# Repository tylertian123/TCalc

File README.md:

# TCalc
Source code for an STM32 calculator. This repository contains the firmware source code for both the main and keyboard processors as well as the custom schematics.

Some notable features:
* Full math expression display engine
* Multi-function graphing
* Support for custom variable and function definitions
* Basic linear algebra capabilities
* Useful built-in functions such as linear system solver, polynomial regression, etc
* Built-in periodic table with extensive information for every element
* Snake and Tetris mini-games
* [Here's it playing Bad Apple because why not.](https://youtu.be/kNUgEzcHYEs) [[Separate repo here]](https://github.com/tylertian123/tcalc-badapple)

## Gallery

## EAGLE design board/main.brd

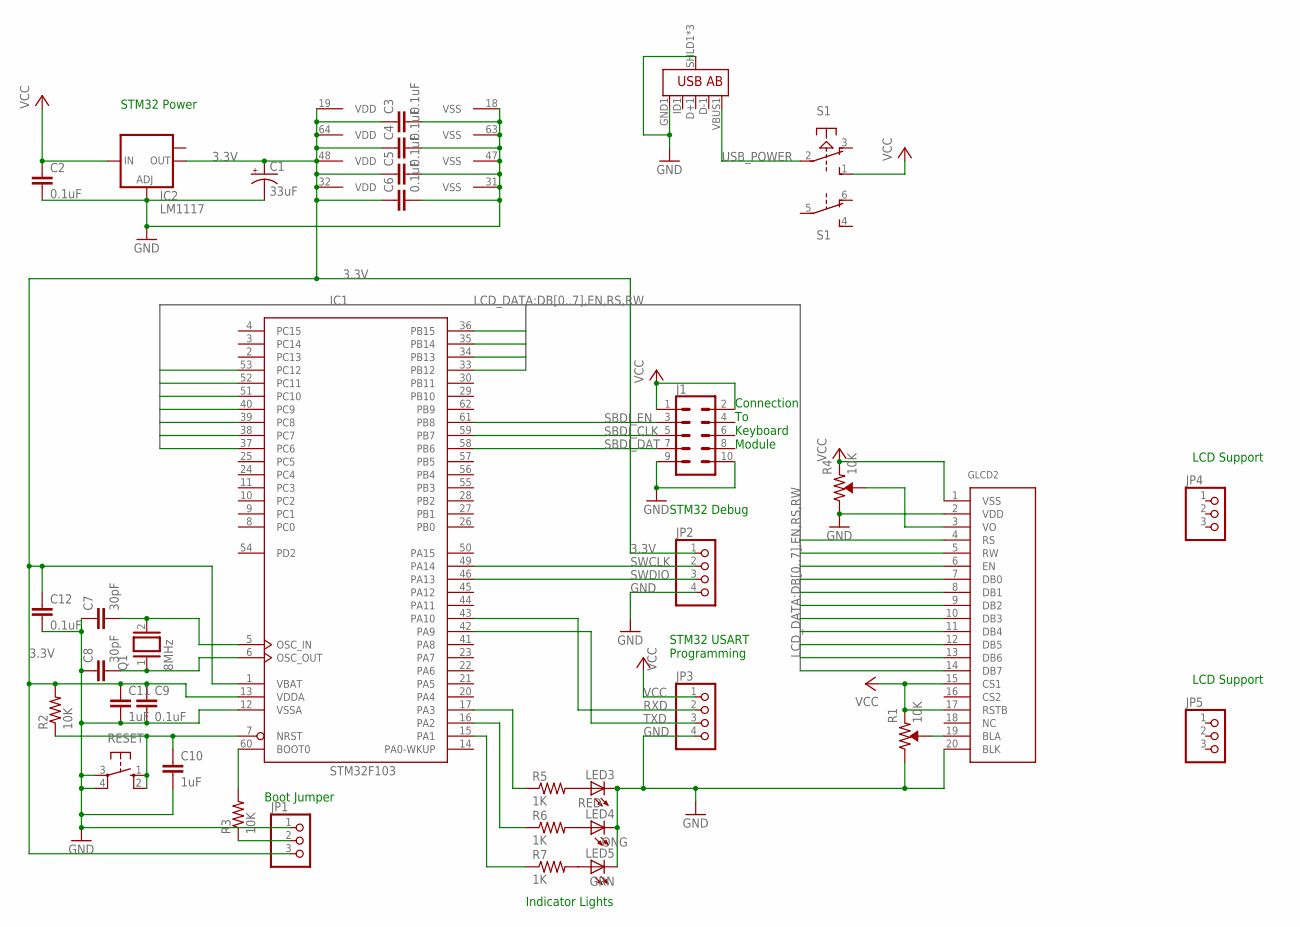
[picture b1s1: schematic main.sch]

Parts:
C1: 33uF; E2-5
C2, C3, C4, C5, C6, C9, C12: 0.1uF; C025-025X050
C7, C8: 30pF; C025-025X050
C10, C11: 1uF; C025-025X050
GLCD2: LCD128X64; GLCD_TRULY_128X64_20_PINES
IC1: STM32F103; LQFP64
IC2: LM1117; SOT223
J1: CONN_05X2SHD_LOCK; 2X5-SHROUDED_LOCK
JP1, JP4, JP5: PINHD-1X3; 1X03
JP2, JP3: PINHD-1X4; 1X04
LED3: RED; LED5MM
LED4: ONG; LED5MM
LED5: GRN; LED5MM
Q1: 8MHz; QS
R1, R4: 10K; TRIMPOT-PTH-3386U
R2, R3: 10K; 0204/7
R5, R6, R7: 1K; 0204/7
RESET: 10-XX; B3F-10XX
S1: PVA2R
U1: USB_AB_SMT; USB-AB-MICRO-SMD

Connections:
3.3V: C1.+, C3.1, C4.1, C5.1, C6.1, C9.1, C11.1, C12.1, IC1.1 (VBAT), IC1.13 (VDDA), IC1.19 (VDD), IC1.32 (VDD), IC1.48 (VDD), IC1.64 (VDD), IC2.2 (OUT), JP1.3, JP2.1, R2.2
DB0: GLCD2.7 (DB0), IC1.33 (PB12)
DB1: GLCD2.8 (DB1), IC1.34 (PB13)
DB2: GLCD2.9 (DB2), IC1.35 (PB14)
DB3: GLCD2.10 (DB3), IC1.36 (PB15)
DB4: GLCD2.11 (DB4), IC1.37 (PC6)
DB5: GLCD2.12 (DB5), IC1.38 (PC7)
DB6: GLCD2.13 (DB6), IC1.39 (PC8)
DB7: GLCD2.14 (DB7), IC1.40 (PC9)
EN: GLCD2.6 (EN), IC1.53 (PC12)
GND: C1.-, C2.2, C3.2, C4.2, C5.2, C6.2, C7.1, C8.1, C9.2, C10.2, C11.2, C12.2, GLCD2.2 (VDD), GLCD2.20 (BLK), IC1.12 (VSSA), IC1.18 (VSS), IC1.31 (VSS), IC1.47 (VSS), IC1.63 (VSS), IC2.1 (ADJ), J1.9, J1.10, JP1.1, JP2.4, JP3.4, LED3.K (C), LED4.K (C), LED5.K (C), R1.1, R4.1, RESET.3, RESET.4 (P1), U1.GND1 (GND), U1.SHLD1 (SHIELD), U1.SHLD2 (SHIELD), U1.SHLD3 (SHIELD)
unnamed: GLCD2.19 (BLA), R1.2
unnamed: GLCD2.3 (VO), R4.2
unnamed: LED3.A, R5.2
unnamed: LED4.A, R6.2
unnamed: C7.2, IC1.5 (OSC_IN), Q1.2
unnamed: C10.1, IC1.7 (NRST), R2.1, RESET.1 (S), RESET.2 (S1)
unnamed: C8.2, IC1.6 (OSC_OUT), Q1.1
unnamed: IC1.15 (PA1), R7.1
unnamed: IC1.60 (BOOT0), R3.2
unnamed: JP1.2, R3.1
unnamed: IC1.16 (PA2), R6.1
unnamed: IC1.17 (PA3), R5.1
unnamed: LED5.A, R7.2
RS: GLCD2.4 (RS), IC1.51 (PC10)
RW: GLCD2.5 (RW), IC1.52 (PC11)
RXD: IC1.43 (PA10), JP3.2
SBDI_CLK: IC1.59 (PB7), J1.5
SBDI_DAT: IC1.58 (PB6), J1.7
SBDI_EN: IC1.61 (PB8), J1.3
SWCLK: IC1.49 (PA14), JP2.2
SWDIO: IC1.46 (PA13), JP2.3
TXD: IC1.42 (PA9), JP3.3
USB_POWER: S1.2, U1.VBUS1 (VBUS)
VCC: C2.1, GLCD2.1 (VSS), GLCD2.15 (CS1), GLCD2.17 (RSTB), IC2.3 (IN), J1.1, J1.2, JP3.1, R1.3, R4.3, S1.1 (S)

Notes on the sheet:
STM32 Power
Boot Jumper
STM32 Debug
STM32 USART Programming
Indicator Lights
LCD Support
Connection To Keyboard Module

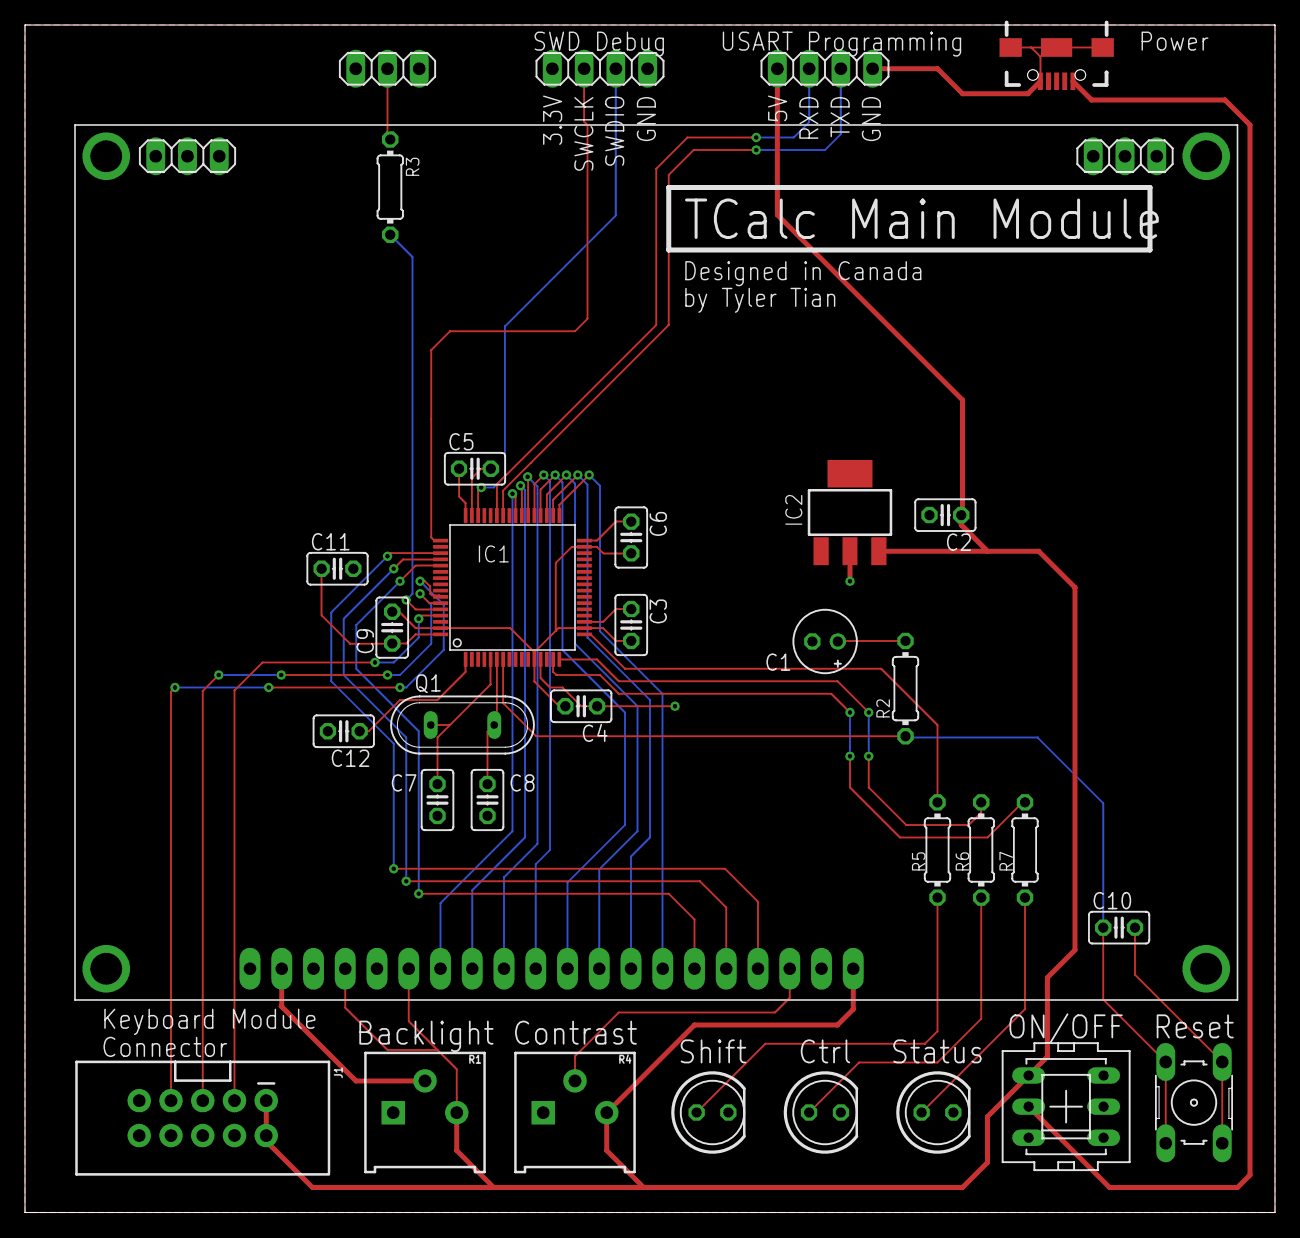
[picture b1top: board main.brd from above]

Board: 2 copper layers, 100.0 x 95.0 mm, 35 parts (0 on the bottom side), 35 nets.

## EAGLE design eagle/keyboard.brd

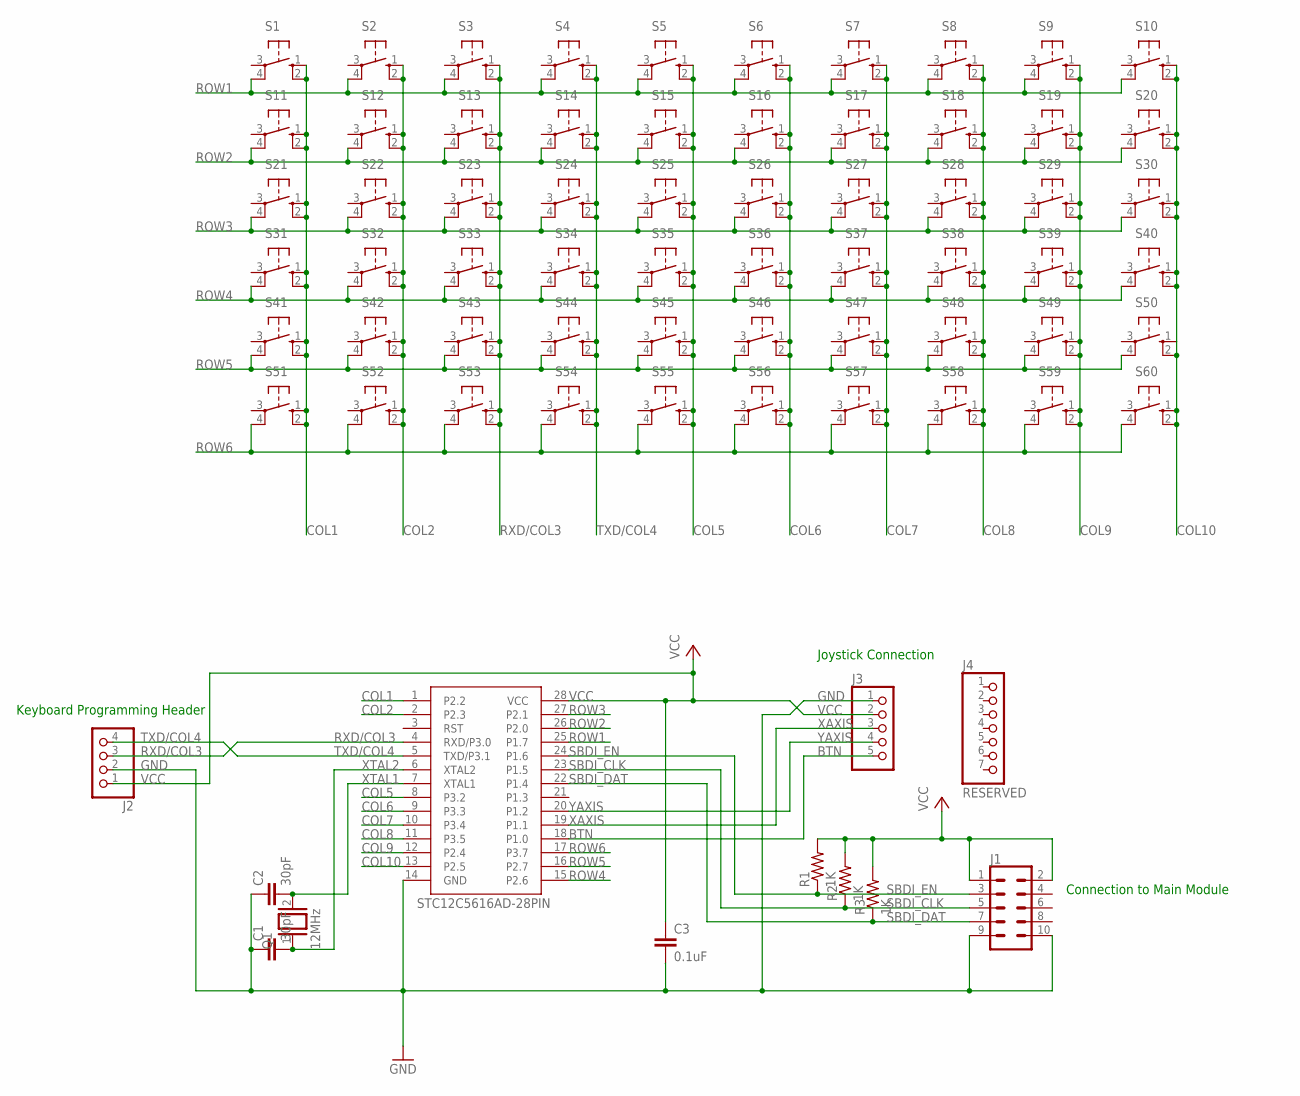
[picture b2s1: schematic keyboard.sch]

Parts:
C1, C2: 30pF; C025-025X050
C3: 0.1uF; C025-030X050
IC1: STC12C5616AD; DIP787W45P254L3505H508Q28B
J1: CONN_05X2SHD_LOCK; 2X5-SHROUDED_LOCK
J2: PINHD-1X4; 1X04
J3: PINHD-1X5; 1X05
J4: RESERVED; 1X07
Q1: 12MHz; QS
R1, R2, R3: 1K; 0204/7
S1, S2, S3, S4, S5, S6, S7, S8, S9, S10, S11, S12, S13, S14, S15, S16, S17, S18, S19, S20, S21, S22, S23, S24, S25, S26, S27, S28, S29, S30, S31, S32, S33, S34, S35, S36, S37, S38, S39, S40, S41, S42, S43, S44, S45, S46, S47, S48, S49, S50, S51, S52, S53, S54, S55, S56, S57, S58, S59, S60: 10-XX; B3F-10XX

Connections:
BTN: IC1.18 (P1.0), J3.5
COL1: IC1.1 (P2.2), S1.1 (S), S1.2 (S1), S11.1 (S), S11.2 (S1), S21.1 (S), S21.2 (S1), S31.1 (S), S31.2 (S1), S41.1 (S), S41.2 (S1), S51.1 (S), S51.2 (S1)
COL2: IC1.2 (P2.3), S2.1 (S), S2.2 (S1), S12.1 (S), S12.2 (S1), S22.1 (S), S22.2 (S1), S32.1 (S), S32.2 (S1), S42.1 (S), S42.2 (S1), S52.1 (S), S52.2 (S1)
COL5: IC1.8 (P3.2), S5.1 (S), S5.2 (S1), S15.1 (S), S15.2 (S1), S25.1 (S), S25.2 (S1), S35.1 (S), S35.2 (S1), S45.1 (S), S45.2 (S1), S55.1 (S), S55.2 (S1)
COL6: IC1.9 (P3.3), S6.1 (S), S6.2 (S1), S16.1 (S), S16.2 (S1), S26.1 (S), S26.2 (S1), S36.1 (S), S36.2 (S1), S46.1 (S), S46.2 (S1), S56.1 (S), S56.2 (S1)
COL7: IC1.10 (P3.4), S7.1 (S), S7.2 (S1), S17.1 (S), S17.2 (S1), S27.1 (S), S27.2 (S1), S37.1 (S), S37.2 (S1), S47.1 (S), S47.2 (S1), S57.1 (S), S57.2 (S1)
COL8: IC1.11 (P3.5), S8.1 (S), S8.2 (S1), S18.1 (S), S18.2 (S1), S28.1 (S), S28.2 (S1), S38.1 (S), S38.2 (S1), S48.1 (S), S48.2 (S1), S58.1 (S), S58.2 (S1)
COL9: IC1.12 (P2.4), S9.1 (S), S9.2 (S1), S19.1 (S), S19.2 (S1), S29.1 (S), S29.2 (S1), S39.1 (S), S39.2 (S1), S49.1 (S), S49.2 (S1), S59.1 (S), S59.2 (S1)
COL10: IC1.13 (P2.5), S10.1 (S), S10.2 (S1), S20.1 (S), S20.2 (S1), S30.1 (S), S30.2 (S1), S40.1 (S), S40.2 (S1), S50.1 (S), S50.2 (S1), S60.1 (S), S60.2 (S1)
GND: C1.1, C2.1, C3.2, IC1.14 (GND), J1.9, J1.10, J2.2, J3.1; also elsewhere on the board
unnamed 10: IC1.3 (RST); also elsewhere on the board
ROW1: IC1.25 (P1.7), S1.4 (P1), S2.4 (P1), S3.4 (P1), S4.4 (P1), S5.4 (P1), S6.4 (P1), S7.4 (P1), S8.4 (P1), S9.4 (P1), S10.4 (P1)
ROW2: IC1.26 (P2.0), S11.4 (P1), S12.4 (P1), S13.4 (P1), S14.4 (P1), S15.4 (P1), S16.4 (P1), S17.4 (P1), S18.4 (P1), S19.4 (P1), S20.4 (P1)
ROW3: IC1.27 (P2.1), S21.4 (P1), S22.4 (P1), S23.4 (P1), S24.4 (P1), S25.4 (P1), S26.4 (P1), S27.4 (P1), S28.4 (P1), S29.4 (P1), S30.4 (P1)
ROW4: IC1.15 (P2.6), S31.4 (P1), S32.4 (P1), S33.4 (P1), S34.4 (P1), S35.4 (P1), S36.4 (P1), S37.4 (P1), S38.4 (P1), S39.4 (P1), S40.4 (P1)
ROW5: IC1.16 (P2.7), S41.4 (P1), S42.4 (P1), S43.4 (P1), S44.4 (P1), S45.4 (P1), S46.4 (P1), S47.4 (P1), S48.4 (P1), S49.4 (P1), S50.4 (P1)
ROW6: IC1.17 (P3.7), S51.4 (P1), S52.4 (P1), S53.4 (P1), S54.4 (P1), S55.4 (P1), S56.4 (P1), S57.4 (P1), S58.4 (P1), S59.4 (P1), S60.4 (P1)
RXD/COL3: IC1.4 (RXD/P3.0), J2.3, S3.1 (S), S3.2 (S1), S13.1 (S), S13.2 (S1), S23.1 (S), S23.2 (S1), S33.1 (S), S33.2 (S1), S43.1 (S), S43.2 (S1), S53.1 (S), S53.2 (S1)
SBDI_CLK: IC1.23 (P1.5), J1.5, R2.1
SBDI_DAT: IC1.22 (P1.4), J1.7, R3.1
SBDI_EN: IC1.24 (P1.6), J1.3, R1.1
TXD/COL4: IC1.5 (TXD/P3.1), J2.4, S4.1 (S), S4.2 (S1), S14.1 (S), S14.2 (S1), S24.1 (S), S24.2 (S1), S34.1 (S), S34.2 (S1), S44.1 (S), S44.2 (S1), S54.1 (S), S54.2 (S1)
VCC: C3.1, IC1.28 (VCC), J1.1, J1.2, J2.1, J3.2, R1.2, R2.2, R3.2; also elsewhere on the board
XAXIS: IC1.19 (P1.1), J3.3
XTAL1: C2.2, IC1.7 (XTAL1), Q1.2
XTAL2: C1.2, IC1.6 (XTAL2), Q1.1
YAXIS: IC1.20 (P1.2), J3.4

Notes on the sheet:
Keyboard Programming Header
Joystick Connection
Connection to Main Module

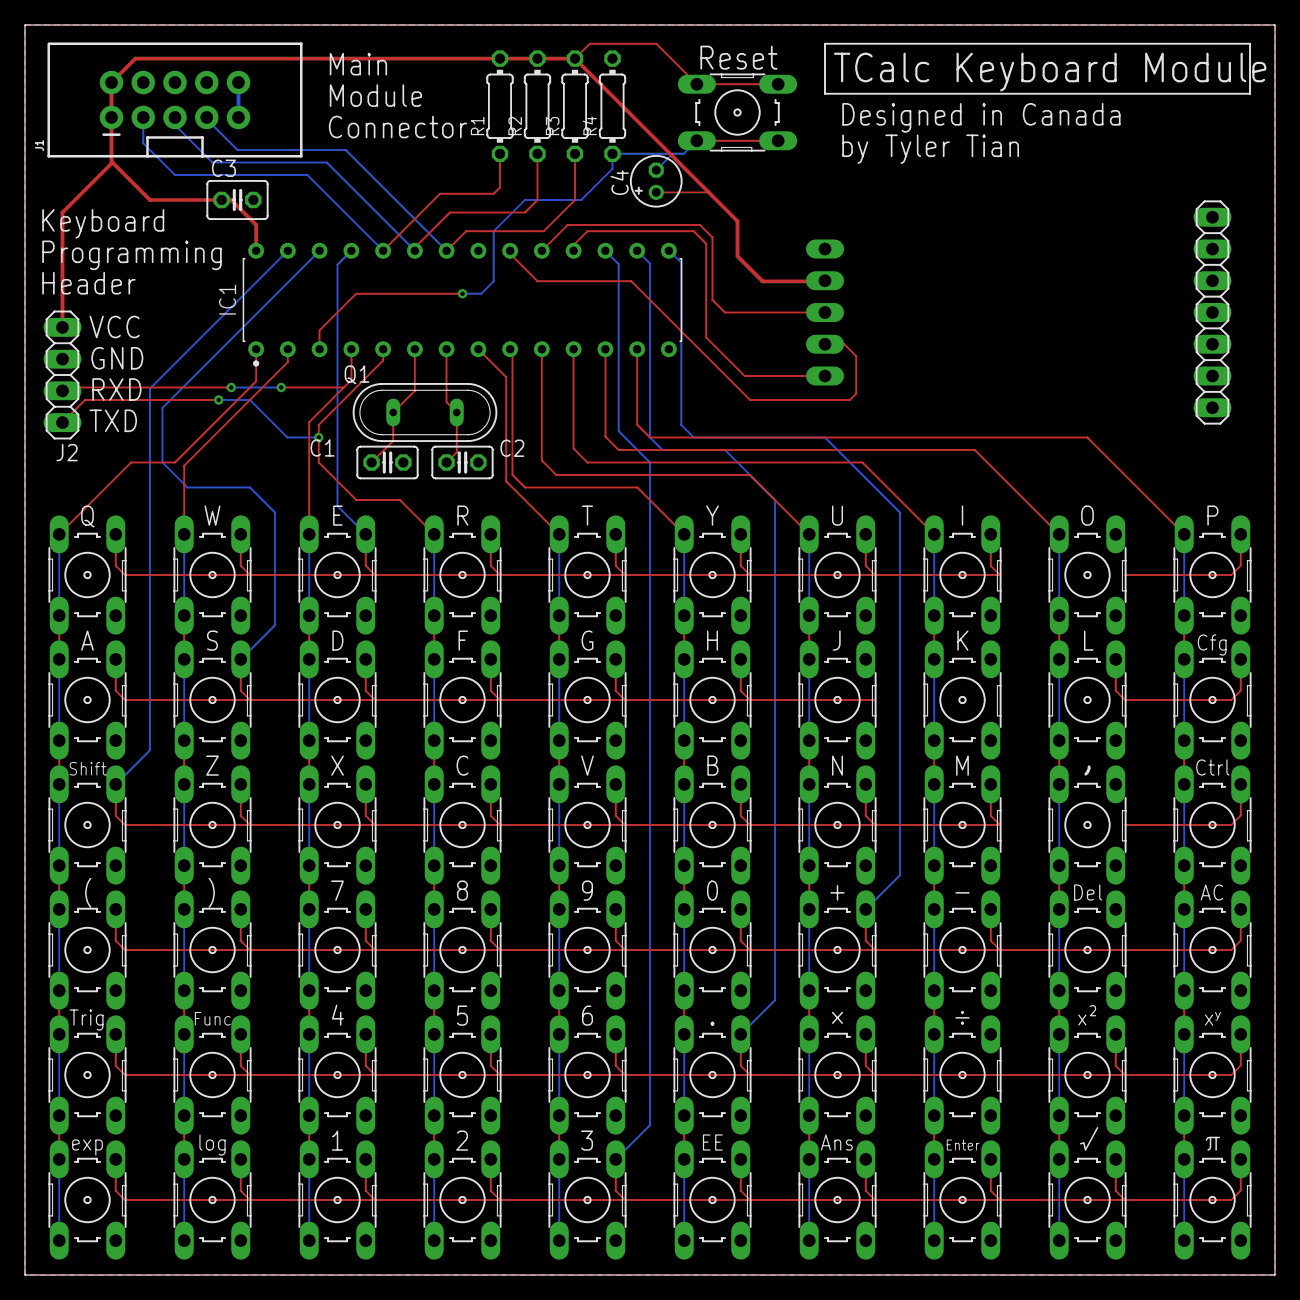
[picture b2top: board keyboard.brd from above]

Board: 2 copper layers, 100.0 x 100.0 mm, 75 parts (1 on the bottom side), 27 nets.

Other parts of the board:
C4: 10uF; E1,8-4
R4: 10K; 0204/7
S61: B3F-10XX

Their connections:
GND: R4.2; also elsewhere on the board
unnamed 10: C4.-, R4.1, S61.3, S61.4; also elsewhere on the board
VCC: C4.+, S61.1, S61.2; also elsewhere on the board

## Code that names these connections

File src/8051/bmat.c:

#include "bmat.h"

void bmat_delay (unsigned int a){
	unsigned int i;
	while( --a != 0){
		for(i = 0; i < 600; i++);
	}
}

void resetRows() {
	ROW1 = ROW2 = ROW3 = ROW4 = ROW5 = ROW6 = 1;
}
void resetCols() {
	COL1 = COL2 = COL3 = COL4 = COL5 = COL6 = COL7 = COL8 = COL9 = COL10 = 1;
}

unsigned char checkCols() {
	if(!COL1) {
		//DEBOUNCE(COL1);
		return 0;
	}
	if(!COL2) {
		//DEBOUNCE(COL2);
		return 1;
	}
	if(!COL3) {
		//DEBOUNCE(COL3);
		return 2;
	}
	if(!COL4) {
		//DEBOUNCE(COL4);
		return 3;
	}
	if(!COL5) {
		//DEBOUNCE(COL5);
		return 4;
	}
	if(!COL6) {
		//DEBOUNCE(COL6);
		return 5;
	}
	if(!COL7) {
		//DEBOUNCE(COL7);
		return 6;
	}
	if(!COL8) {
		//DEBOUNCE(COL8);
		return 7;
	}
	if(!COL9) {
		//DEBOUNCE(COL9);
		return 8;
	}
	if(!COL10) {
		//DEBOUNCE(COL10);
		return 9;
	}
	return 0xFF;
}

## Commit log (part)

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2018-12-14 Add simple incomplete support for multiple arguments
2018-12-14 Fix memory leaks
2018-12-14 Fix bug in ntoa
2018-12-15 Add code for evaluating user-defined functions
2018-12-16 Add basic implementation of defining functions
2018-12-17 Add new round function
2018-12-18 Change signature of Function::compute
2018-12-18 Add function catalogue
2018-12-18 Overload call operator of eval::Operator
2018-12-19 Remap some keys and add function definition recall
2018-12-24 Check in eagle schs
2018-12-24 Fix schematic button matrix
2018-12-24 Add silkscreen
2018-12-25 Restore accidentally deleted file
2018-12-25 Finish basic component placement
2018-12-25 Add silkscreen labels
2018-12-26 Reexport gerbers
2018-12-26 Improve silkscreen
2018-12-27 Reroute main board
2019-06-25 Change port defs and fix interrupts
    Change port definitions for 8051 for the PCB design. Fix broken
    interrupts by adding calls to GPIO_EXTILineConfig.
2019-06-26 Add base for neda::Matrix
2019-06-26 Add matrix key in 8051 chip
2019-06-26 Fix neda::Matrix crashing bug
    Fix neda::Matrix crashing bug caused by the previous changing all
    indexes to be 0-based.
2019-06-27 Add matrix parsing in eval
2019-06-28 Add support for matrix addition, subtraction and multiplication
2019-06-28 Add support for matrix-scalar multiplication and division
2019-07-03 Add vector cross product for R3
2019-07-04 Add eval::Matrix::eliminate()
    Add new function to eval::Matrix that performs Gaussian elimination.
2019-07-04 Add identity matrix function
    Add built-in function I() which evaluates to an identity matrix of a
    specified dimension.
2019-07-04 Add result scrolling
    Add ability to scroll results that are too wide or too tall to fit on
    the screen.
2019-07-04 Reduce SBDI transmission speed
    Reduce SBDI transmission speed by 1/2 to prevent bad key readings.
2019-07-05 Change ifs to switches in eval code
    Change if...else if...else chains in eval::Operator::operator() into
    switch statements.
2019-07-05 Improve matrix drawing
    Centre expressions horizontally when drawing matrices.
2019-07-06 Remove unused characters and change division sign
    Comment out unused characters in font.cpp and change the division symbol
    to be the same as the slash.
2019-07-06 Add option to set number of significant digits
2019-07-08 Copy normal key press handling into exprentry.cpp
    Copy key press handling in normal (expression edit) mode into
    expr::ExprEntry.
2019-07-08 Copy remaining key handlers to exprentry
    Copy key handlers for config and matrix menus into expr::ExprEntry.
2019-07-08 Add new characters and update old characters
    Add new greater than or equal to and less than or equal to characters
    and update the old greater than and less than characters.
2019-07-09 Add eval code for piecewise functions
    Add code to evaluate piecewise functions.
2019-07-09 Add "else" clause in piecewise functions
    Add ability to specify an "else" clause in piecewise functions.
2019-07-09 Fix bug with expr::ExprEntry::adjustExpr()
    Fix bug where adjustExpr() sometimes positions the expression in the
    wrong location due to incorrect cursor info due to the locations of
    expressions not being updated.
2019-07-10 Change key enums
    Change key enums from sequential to randomized in the range from
    0x0000-0xFFFF inclusive. This means that now two bit flips (which would
    not be detected by the parity checking) is now less likely to generate
    another valid key combo.
2019-07-10 Fix shift light not turning off issue
    Fix shift light not turning off issue caused by an issue in the SBDI
    bus.
2019-07-11 Change key mappings on keyboard
    Move graph function selection to Ctrl+F and make Ctrl+G graph.
2019-07-11 Fix DrawBuf bugs and use in LCD12864
    Delegate drawing functions in LCD12864 to DrawBuf. Fix bugs in
    DrawBuf::setPixel and drawBuf::drawImage.
2019-07-11 Fix bugs in basic graphing code
2019-07-11 Fix bug and improve UI for graphing
    Fix bug where the screen will flicker when transitioning from graph
    viewer back to normal mode. Allow going into graph settings and graph
    function selection menues from the graph viewer.
2019-07-11 Add a cursor to the graph viewer
    Add a cursor in graph viewer mode that shows the X and Y coordinates.
2019-07-12 Create struct eval::Variable
    Create struct eval::Variable to replace the two separate arrays for
    variable names and variable values.
2019-07-16 Add new characters to LCD charset
    Add new logic operators to LCD charset, including AND, OR, XOR and NOT.
2019-07-17 Fix bug where logical operators treat undefined as true
    Fix bug where the logical operators AND, OR and XOR treat undefined
    values as if they were true.
2019-07-17 Fix bug introduced by commit 0b8f178
    Fix a bug introduced by commit 0b8f178 where the plus and minus
    operators will always be evaluated as unary operators regardless.
2019-07-17 Create unitconv.cpp and unitconv.hpp
    Create unitconv.cpp and unitconv.hpp, which convert between different
    units.
2019-07-21 Fix bug in neda::Matrix::copy() and neda::Piecewise::copy()
    Fix bug in Matrix and Piecewise's copy functions that causes the
    positioning of the copied expression to be messed up because they don't
    set the new expression's top spacing.
2019-07-21 Add key for subscript
    Bind Shift+Exponent to insert a subscript.
2019-07-21 Add null check when calling operators in eval::evaluate()
    When evaluating the expression by calling operators, add null checks in
    case the operation fails.
2019-07-21 Remove redundant built-in functions
    Remove redundant built-in functions transpose, inv, and I as they can
    now be done using a better syntax. Increase version to 1.2.7.
2019-07-21 Remove comparison operator keybinds
    Remove keybinds for the comparison operators greater than, less than,
    greater than or equal to, and less than or equal to since they can now
    be accessed through the logic menu.
2019-07-22 Add mini USART console
    Add a mini USART debug console, enabled by compiling with the
    _USE_CONSOLE macro.
2019-07-22 Add DynamicArray::createConstRef()
    Add a new DynamicArray static method createConstRef() that creates a
    const DynamicArray which just points to the memory specified by two
    iterators, thus avoiding having to allocate more memory and copying over
    elements. Use this new method in evaluate calls().
    Increase the result store count to 5.
2019-07-23 Add area units to conversion table
    Add area units to conversion table, including all units in the length
    units section squared, and hectares and acres. Modify findTokenEnd to
    allow names containing digits to allow this.
2019-07-24 Add stack overflow check to eval::evaluate
    Add a stack pointer check to eval::evaluate() to make sure that
    recursive functions without an exit condition does not cause a crash
    from stack overflow.
    Add command "stackinfo" to the console, which prints out the stack
    beginning and end addresses, stack size and current stack pointer.
    Increase version to 1.2.11.
2019-07-26 Allow matrix to be constructed from column vectors
    Allow the syntax where a matrix can be constructed from a row of column
    vectors.
2019-07-26 Add confirmation dialogs to clear var and all clear keys
    Pressing the clear var and all clear keys will now make a confirmation
    dialog appear to prevent being triggered accidentally.
2019-07-27 Change default increase amount in storage classes
    Change the default increase amount in Deque and DynamicArray from 1 to 8
    to make parsing expressions more efficient.
    Remove templates on eval::freeTokens and move its definition into
    eval.cpp.
2019-07-28 Delete unused files
    Delete unused files (starup_stm32f10x_md.s, stm32f10x_it.h and
    stm32f10x_it.c).
2019-07-29 Implement some operators for Numerical
    Implement operators += and -= for Numerical.
2019-07-29 Add more operators to util::Numerical
    Add == and != operators to util::Numerical.
2019-07-30 Add more operators and methods to util::Numerical
    Add operators < and > to util::Numerical and implement the pow() method
    for it.
2019-07-30 Change implementation of ltoa and ftoa
    Change implementation of ltoa and ftoa to use sprintf instead of doing
    the conversion themselves.
2019-07-31 Implement the fraction-format key
    Implement the fraction-format key to convert result display method from
    improper fractions to mixed numbers.
2019-09-01 Add useful graph viewer mode commands
    Add some useful graph viewer mode commands, including pressing h to
    "home" the cursor, pressing c to move the display window so that the
    cursor is centered, and pressing +/- to zoom in/out around the cursor.
2019-09-01 Add fast cursor movement in graph viewer
    Add feature where the cursor can be moved by 10 pixels each time in the
    graph viewer using the WASD keys.
2019-09-02 Change key enumeration and mapping code
    Change the key enumeration from random to sequential, which allows for a
    better algorithm that maps key code to characters which relies on the
    sequential order of keys for letters and numbers instead of using a
    switch statement.
2019-09-08 Create periodic table data
    Create files for periodic table stuff and add in some basic data for
    every element.
2019-09-18 Add code for periodic table outline
    Add code for displaying the outline of the periodic table.
2019-09-20 Add mean function
    Add a varargs mean function.
2019-09-23 Add basic element display
    Add basic element info display in periodic table mode.
2019-09-25 move to pio
2019-09-25 fix name
2019-09-26 fix ln from win
2019-09-27 Fix compile warnings
    Fix compile warnings due to using NULL in memset, adding brackets around
    && and missing default labels in switch statements.
2019-09-30 Add periodic table search functions
    Add periodic table functions to search by atomic number, symbol or name.
2019-10-02 Refactor drawString()
    Change the signature of lcd::DrawBuf::drawString() to now accept a set
    of flags telling it what to do (e.g. invert and alignment).
2019-10-06 Improve periodic table data
    Add electron configuration to periodic table data and fix bug of the
    valences of known noble gases being unknown.
2019-10-08 Add some processing for Tetris game
    Add some basic game logic for another hidden game - Tetris.
2019-10-08 Add DrawBuf::drawString vertical align flags
    Add the ability to specifiy vertical align in DrawBuf::drawString. Fix
    the misaligned text in Tetris.
2019-10-11 Redirect printf to replace usart::printf
    Redefine _write to use printf directly instead of usart::printf and fix
    heapstats.
2019-10-24 Improve Tetris RNG and add Holds
    Improve the Tetris RNG so that all tetrominoes show up at least once per
    cycle. Add a New Tetris mode with Holds.
2019-11-20 Add analog controls for graph viewer cursor
    Allow the graph viewer cursor to be controlled by the analog stick.
2019-12-06 Tidy up code and add .clang-format
    Add a .clang-format specification, format files and tidy up graphing
    code.
2019-12-07 Add ability to plot points
    Add ability to plot single points with row or column vectors, or a
    dataset with an nx2 matrix.
2019-12-09 Implement linear regression
    Implement linear regression with the linReg(x, y, model...) expression.
2019-12-13 exception handling + backtrace genertaion
2019-12-13 reduce gunzip usage
2019-12-16 Fix custom function evaluation
    Fix bug in custom function evaluation code that causes a crash if a
    custom function is evaluated more than one time (as it was accidentally
    deleted after evaluation).
2019-12-18 Add keyboard reset in fault handler
    Reset the keyboard in the fault handler in case it was in analog mode.
2020-01-13 Add emulator scripts
2020-06-05 Fix unary operators
    Unary operators will no longer always cause a syntax error.

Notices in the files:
parts and their libraries:
SparkFun-Connectors: Licensing: Creative Commons ShareAlike 4.0 International - https://creativecommons.org/licenses/by-sa/4.0
